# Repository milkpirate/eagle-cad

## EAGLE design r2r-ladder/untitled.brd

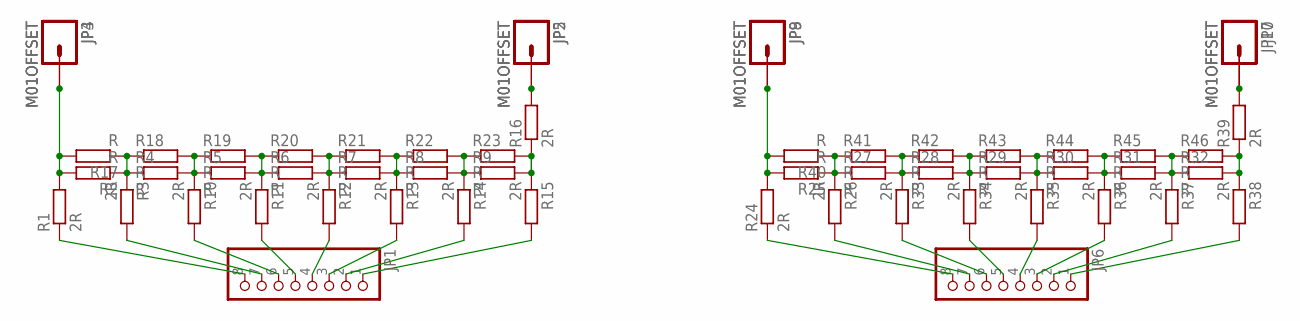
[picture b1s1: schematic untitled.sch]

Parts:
JP1, JP6: PINHD-1X8/90; 1X08/90
JP2, JP3, JP4, JP5, JP7, JP8, JP9, JP10: M01OFFSET; 1X01_OFFSET
R1, R3, R10, R11, R12, R13, R14, R15, R16: 2R; M0805
R2, R4, R5, R6, R7, R8, R9, R17, R18, R19, R20, R21, R22, R23: R; M0805
R24, R26, R33, R34, R35, R36, R37, R38, R39: 2R; 0204V
R25, R27, R28, R29, R30, R31, R32, R40, R41, R42, R43, R44, R45, R46: R; 0204V

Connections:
unnamed: R2.1, R3.1, R4.1
unnamed: R4.2, R5.1, R10.1
unnamed: R5.2, R6.1, R11.1
unnamed: R6.2, R7.1, R12.1
unnamed: R8.2, R9.1, R14.1
unnamed: R7.2, R8.1, R13.1
unnamed: JP3.1, JP4.1, R1.2, R2.2, R17.2
unnamed: JP1.8, R1.1
unnamed: JP1.7, R3.2
unnamed: JP1.6, R10.2
unnamed: JP1.5, R11.2
unnamed: JP1.4, R12.2
unnamed: JP1.3, R13.2
unnamed: JP1.2, R14.2
unnamed: R9.2, R15.1, R16.1
unnamed: JP1.1, R15.2
unnamed: JP2.1, JP5.1, R16.2
unnamed: R25.1, R26.1, R27.1
unnamed: R27.2, R28.1, R33.1
unnamed: R28.2, R29.1, R34.1
unnamed: R29.2, R30.1, R35.1
unnamed: R31.2, R32.1, R37.1
unnamed: R30.2, R31.1, R36.1
unnamed: JP8.1, JP9.1, R24.2, R25.2, R40.2
unnamed: JP6.8, R24.1
unnamed: R17.1, R18.1
unnamed: R18.2, R19.1
unnamed: R19.2, R20.1
unnamed: R20.2, R21.1
unnamed: R22.2, R23.1
unnamed: R21.2, R22.1
unnamed: JP6.7, R26.2
unnamed: JP6.6, R33.2
unnamed: JP6.5, R34.2
unnamed: JP6.4, R35.2
unnamed: JP6.3, R36.2
unnamed: JP6.2, R37.2
unnamed: R32.2, R38.1, R39.1, R46.2
unnamed: JP6.1, R38.2
unnamed: JP7.1, JP10.1, R39.2
unnamed: R40.1, R41.1
unnamed: R41.2, R42.1
unnamed: R42.2, R43.1
unnamed: R43.2, R44.1
unnamed: R45.2, R46.1
unnamed: R44.2, R45.1

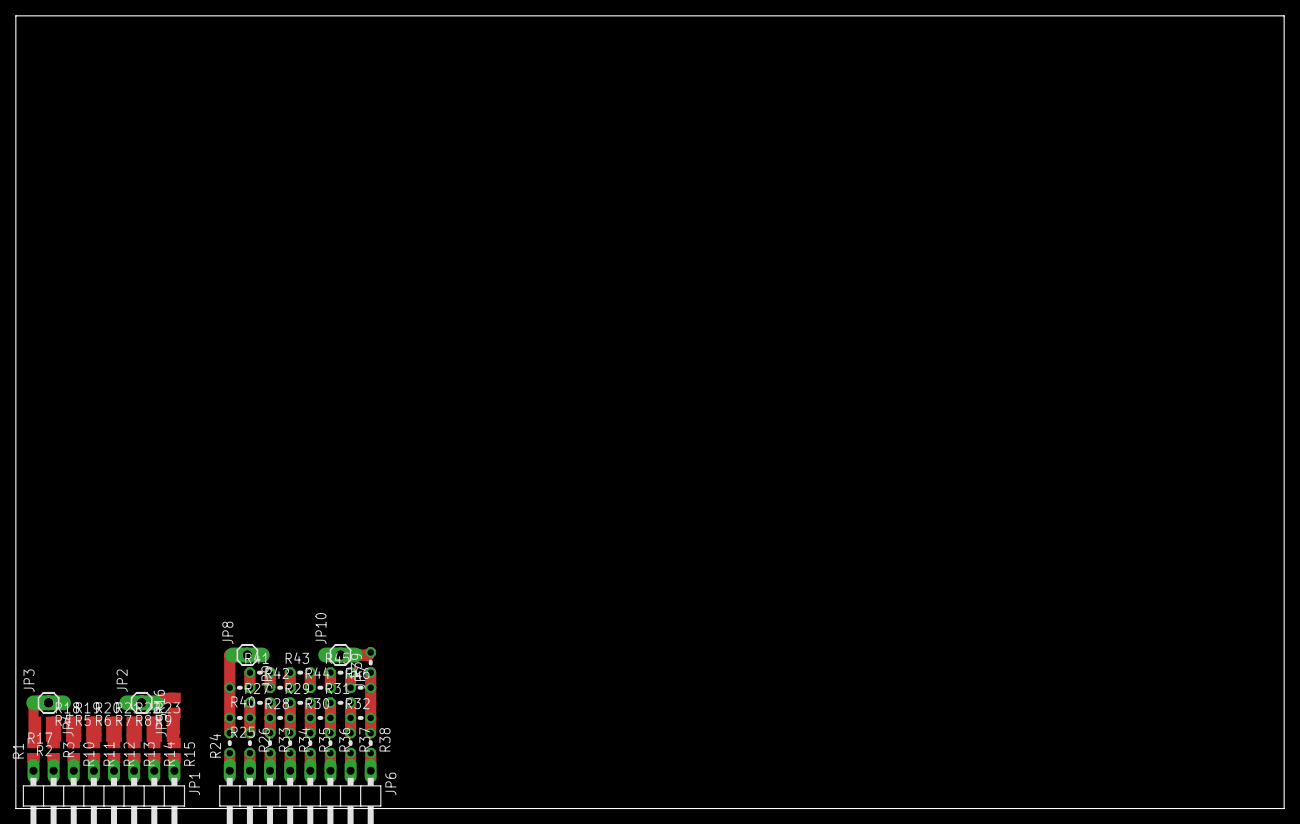
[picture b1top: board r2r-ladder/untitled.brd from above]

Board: 2 copper layers, 160.0 x 100.0 mm, 56 parts (0 on the bottom side), 46 nets.

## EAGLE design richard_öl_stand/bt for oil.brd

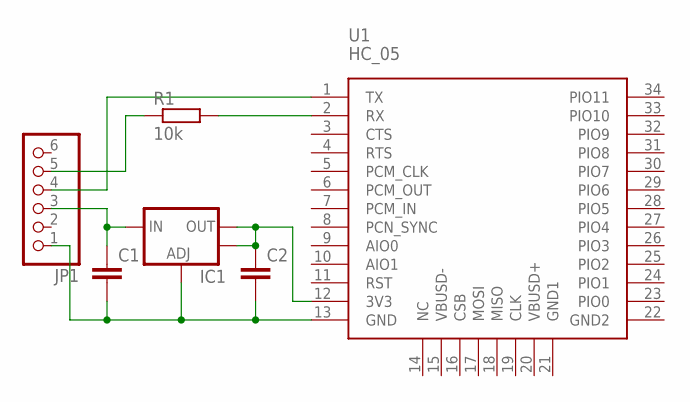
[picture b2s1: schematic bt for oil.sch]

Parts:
C1, C2: C-EUC0805; C0805
IC1: V_REG_LM1117SOT223; SOT223
JP1: PINHD-1X6/90; 1X06/90
R1: 10k; M0805
U1: HC_05; BLUETOOTH_SMD

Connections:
3V3: C2.1, IC1.2 (OUT), IC1.4 (OUT), U1.12 (3V3)
5V: C1.1, IC1.3 (IN), JP1.3
GND: C1.2, C2.2, IC1.1 (ADJ), JP1.1, U1.13 (GND)
unnamed: R1.2, U1.2 (RX)
RX: JP1.5, R1.1
TX: JP1.4, U1.1 (TX)

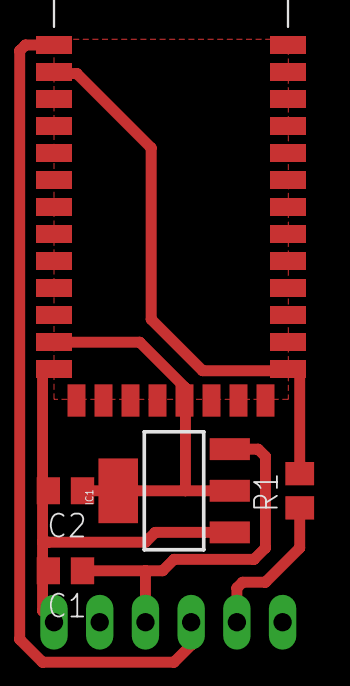
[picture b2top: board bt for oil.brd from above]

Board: 2 copper layers, 6 parts (1 on the bottom side), 6 nets.

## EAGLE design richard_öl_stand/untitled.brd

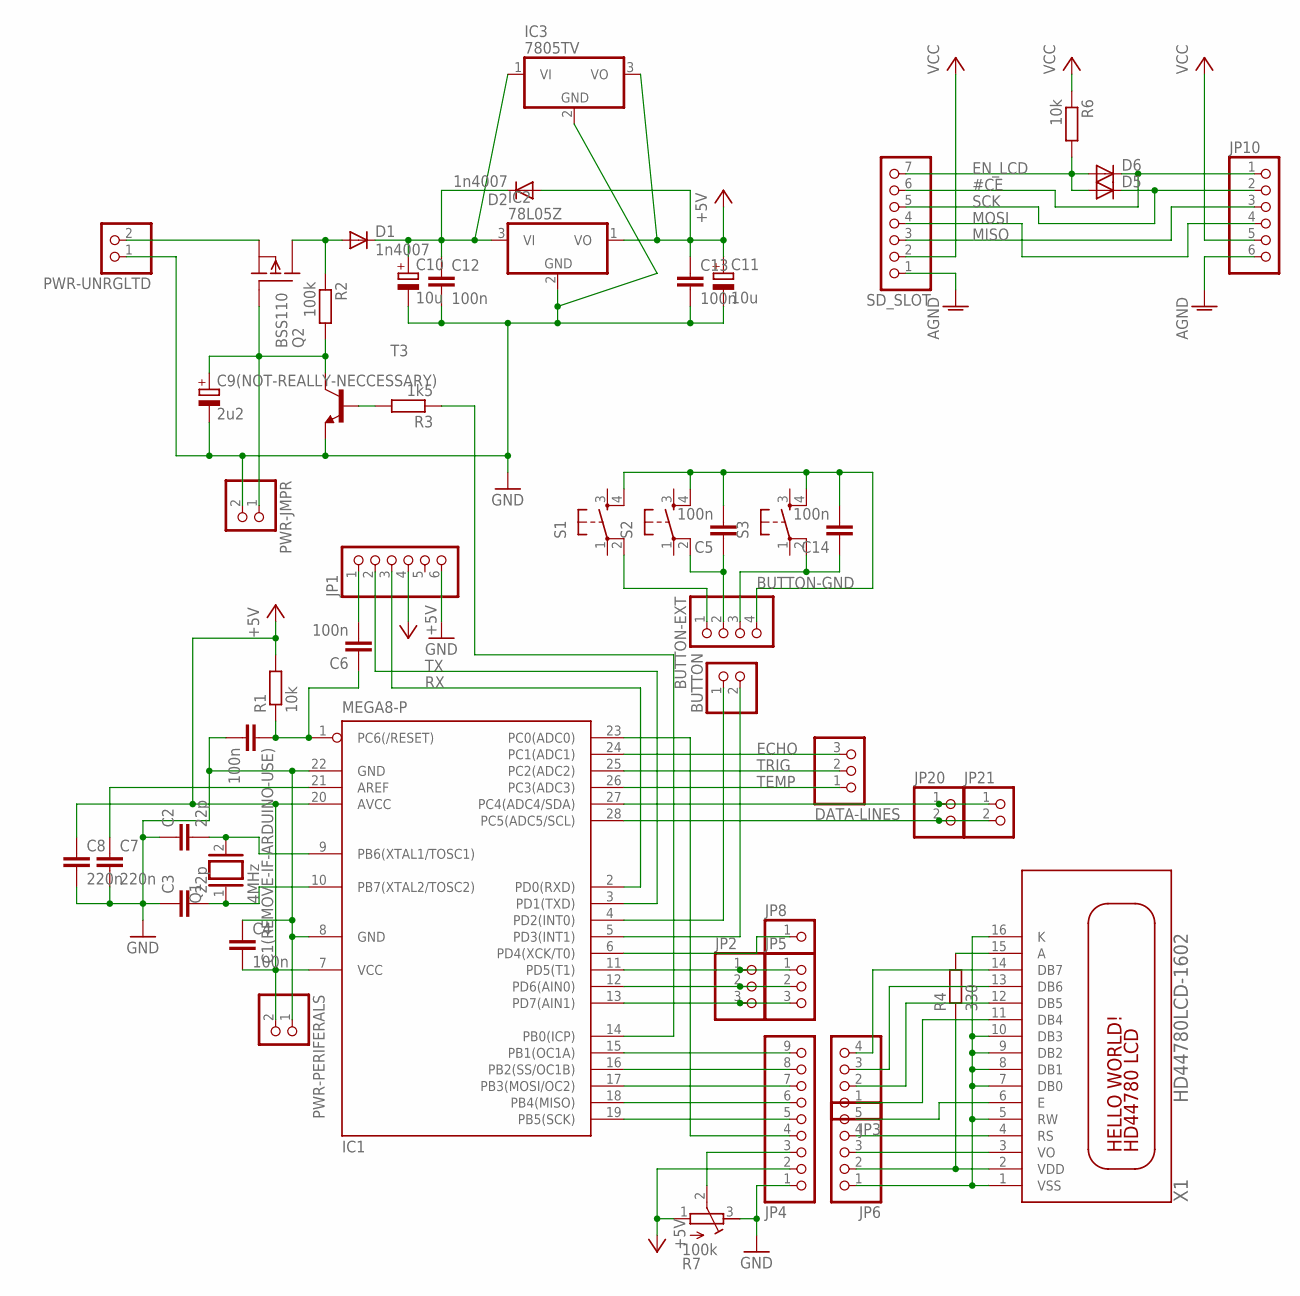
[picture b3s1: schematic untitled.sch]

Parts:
BUTTON: PINHD-1X2; 1X02
BUTTON-EXT: PINHD-1X4; 1X04
C1(REMOVE-IF-ARDUINO-USE), C4, C5, C6, C12, C13, C14: 100n; C025-025X050
C2, C3: 22p; C025-025X050
C7, C8: 220n; C025-025X050
C9(NOT-REALLY-NECCESSARY): 2u2; E2,5-6
C10: 10u; E2,5-6
C11: 10u; E5R
D1, D2: 1n4007; D-2.5
D5: DIODE-D-5; D-5
D6: DIODE-D-2.5; D-2.5
DATA-LINES: PINHD-1X3; 1X03
IC1: MEGA8-P; DIL28-3
IC2: 78L05Z; TO92
IC3: 7805TV; TO220V
JP1, JP10: PINHD-1X6; 1X06
JP2, JP5: PINHD-1X3; 1X03
JP3: PINHD-1X4; 1X04
JP4: PINHD-1X9; 1X09
JP6: PINHD-1X5; 1X05
JP8: PINHD-1X1; 1X01
JP20, JP21: PINHD-1X2; 1X02
PWR-JMPR: PINHD-1X2; 1X02
PWR-PERIFERALS: PINHD-1X2; 1X02
PWR-UNRGLTD: PINHD-1X2; 1X02
Q1: 4MHz; QS
Q2: BSS110; TO92
R1: 10k; 0207/2V
R2: 100k; 0207/2V
R3: 1k5; 0207/2V
R4: 330; 0207/10
R6: 10k; 0207/12
R7: 100k; RTRIM64W
S1, S2, S3: TAC_SWITCHPTH; TACTILE-PTH
SD_SLOT: PINHD-1X7; 1X07
T3: BC167-NPN-TO92-ECB; TO92-ECB
X1: HD44780LCD-1602; LCD1602

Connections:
#CE: D6.C, JP10.1, SD_SLOT.6
+5V: C4.2, C8.1, C11.+, C13.1, D2.A, IC1.7 (VCC), IC1.20 (AVCC), IC2.1 (VO), IC3.3 (VO), JP1.4, JP4.2, PWR-PERIFERALS.2, R1.2, R7.1 (A)
AGND: JP10.6, SD_SLOT.1
BUTTON-GND: BUTTON-EXT.4, C5.2, C14.2, S1.4, S2.4, S3.4
ECHO: DATA-LINES.3, IC1.24 (PC1(ADC1))
EN_LCD: D5.A, D6.A, R6.2, SD_SLOT.7
GND: C1(REMOVE-IF-ARDUINO-USE).2, C2.1, C3.1, C4.1, C7.2, C8.2, C9(NOT-REALLY-NECCESSARY).-, C10.-, C11.-, C12.2, C13.2, IC1.8 (GND), IC1.22 (GND), IC2.2 (GND), IC3.2 (GND), JP1.6, JP4.1, PWR-JMPR.2, PWR-PERIFERALS.1, PWR-UNRGLTD.1, R7.3 (E), T3.E
MISO: JP10.3, SD_SLOT.3
MOSI: JP10.4, SD_SLOT.4
unnamed: C6.2, JP1.1
unnamed: JP4.3, R7.2 (S)
unnamed: R4.2, X1.15 (A)
unnamed: JP3.2, X1.12 (DB5)
unnamed: JP3.3, X1.13 (DB6)
unnamed: JP3.4, X1.14 (DB7)
unnamed: JP3.1, X1.11 (DB4)
unnamed: JP6.5, X1.6 (E)
unnamed: IC1.15 (PB1(OC1A)), JP4.9
unnamed: JP6.4, X1.4 (RS)
unnamed: JP6.3, X1.3 (VO)
unnamed: IC1.16 (PB2(SS/OC1B)), JP4.8
unnamed: IC1.17 (PB3(MOSI/OC2)), JP4.7
unnamed: IC1.18 (PB4(MISO)), JP4.6
unnamed: IC1.19 (PB5(SCK)), JP4.5
unnamed: IC1.23 (PC0(ADC0)), JP4.4
unnamed: C1(REMOVE-IF-ARDUINO-USE).1, C6.1, IC1.1 (PC6(/RESET)), R1.1
unnamed: BUTTON.1, IC1.4 (PD2(INT0))
unnamed: C2.2, IC1.9 (PB6(XTAL1/TOSC1)), Q1.2
unnamed: C3.2, IC1.10 (PB7(XTAL2/TOSC2)), Q1.1
unnamed: IC1.13 (PD7(AIN1)), JP2.3, JP5.3
unnamed: IC1.12 (PD6(AIN0)), JP2.2, JP5.2
unnamed: C7.1, IC1.21 (AREF)
unnamed: IC1.11 (PD5(T1)), JP2.1, JP5.1
unnamed: C9(NOT-REALLY-NECCESSARY).+, PWR-JMPR.1, Q2.2 (G), R2.2, T3.C
unnamed: R3.2, T3.B
unnamed: BUTTON.2, IC1.5 (PD3(INT1))
unnamed: PWR-UNRGLTD.2, Q2.1 (S)
unnamed: D1.A, Q2.3 (D), R2.1
unnamed: BUTTON-EXT.3, C14.1, S3.2
unnamed: IC1.27 (PC4(ADC4/SDA)), JP20.1, JP21.1
unnamed: IC1.28 (PC5(ADC5/SCL)), JP20.2, JP21.2
unnamed: C10.+, C12.1, D1.C, D2.C, IC2.3 (VI), IC3.1 (VI)
unnamed: IC1.6 (PD4(XCK/T0)), JP8.1
unnamed: BUTTON-EXT.2, C5.1, S2.2
unnamed: IC1.14 (PB0(ICP)), R3.1
unnamed: BUTTON-EXT.1, S1.2
RX: IC1.2 (PD0(RXD)), JP1.3
SCK: D5.C, JP10.2, SD_SLOT.5
TEMP: DATA-LINES.1, IC1.26 (PC3(ADC3))
TRIG: DATA-LINES.2, IC1.25 (PC2(ADC2))
TX: IC1.3 (PD1(TXD)), JP1.2
VCC: JP10.5, R6.1, SD_SLOT.2
VDD: JP6.2, R4.1, X1.2 (VDD)
VSS: JP6.1, X1.1 (VSS), X1.5 (RW), X1.7 (DB0), X1.8 (DB1), X1.9 (DB2), X1.10 (DB3), X1.16 (K)

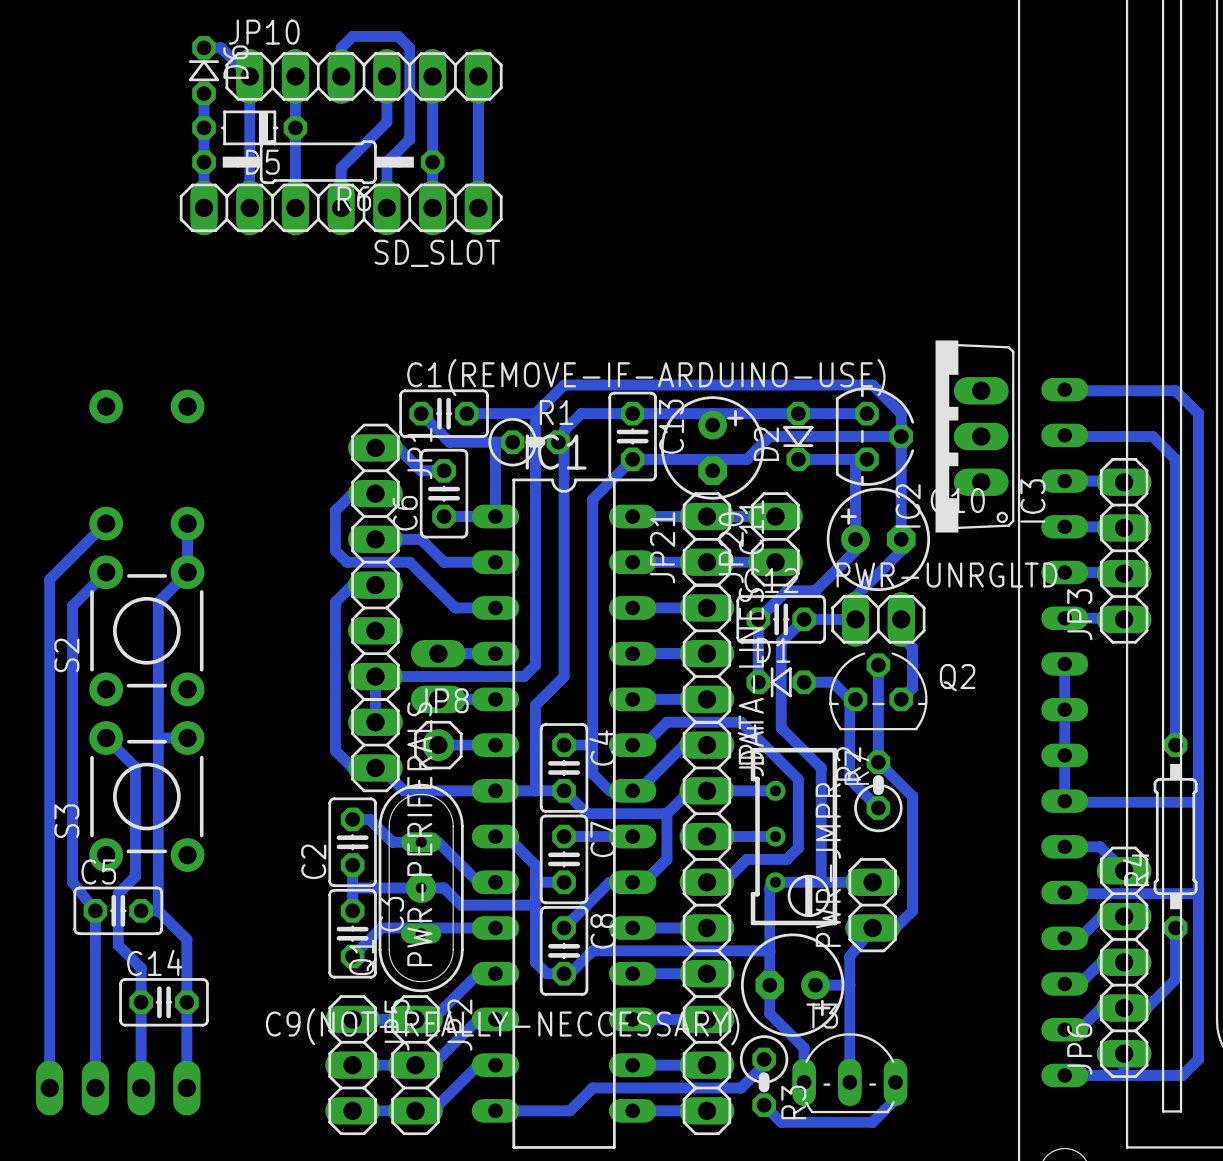
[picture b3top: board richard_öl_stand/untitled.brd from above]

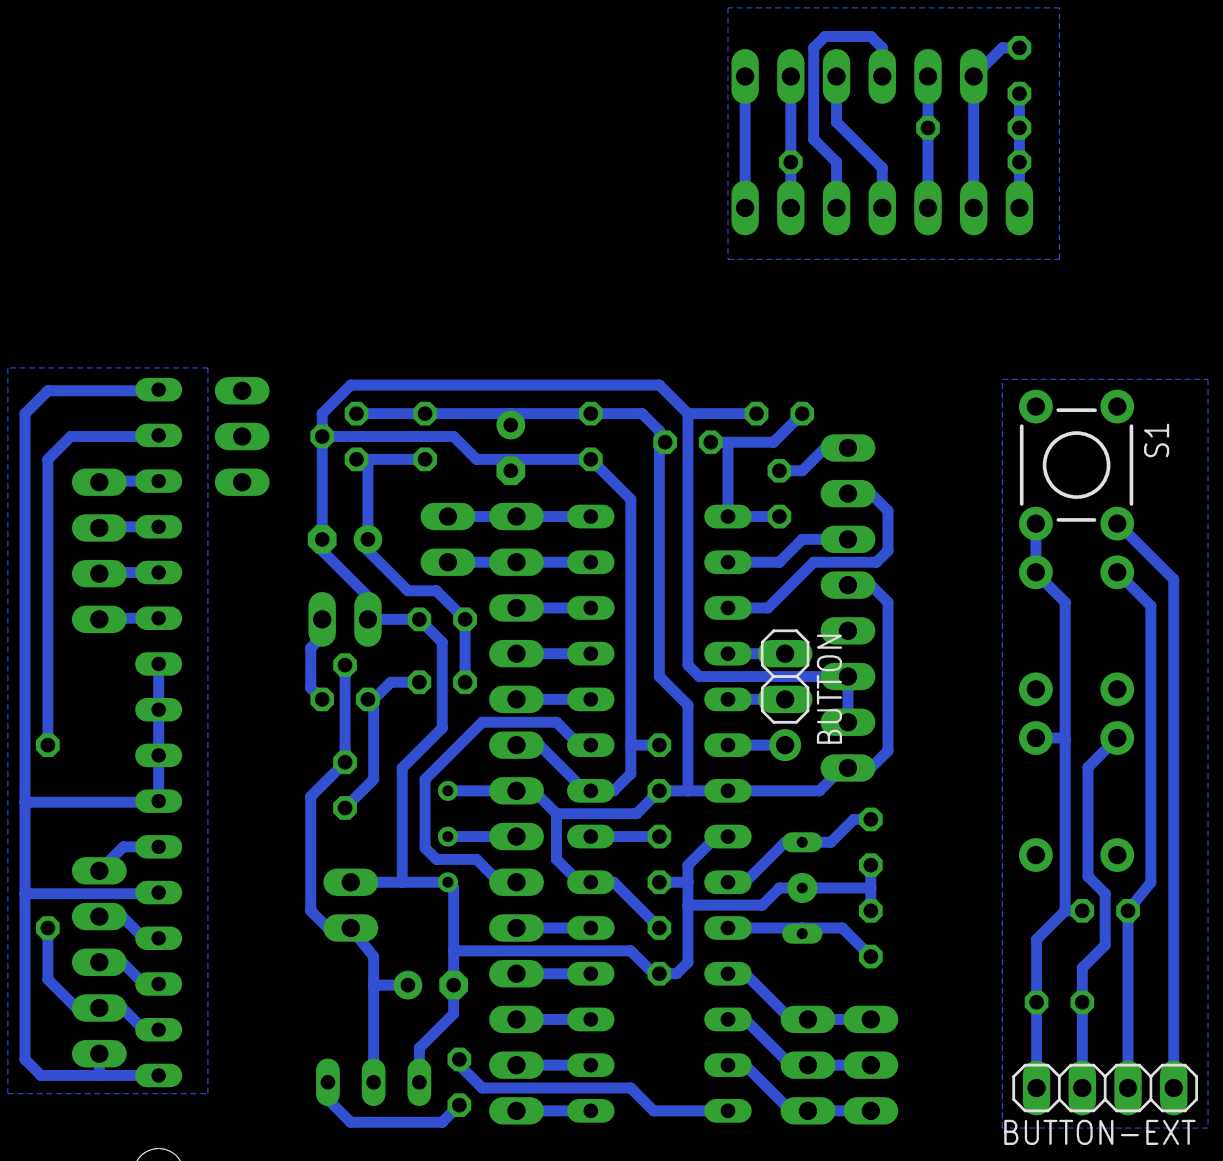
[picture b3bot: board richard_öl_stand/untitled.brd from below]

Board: 2 copper layers, 51 parts (3 on the bottom side), 54 nets.

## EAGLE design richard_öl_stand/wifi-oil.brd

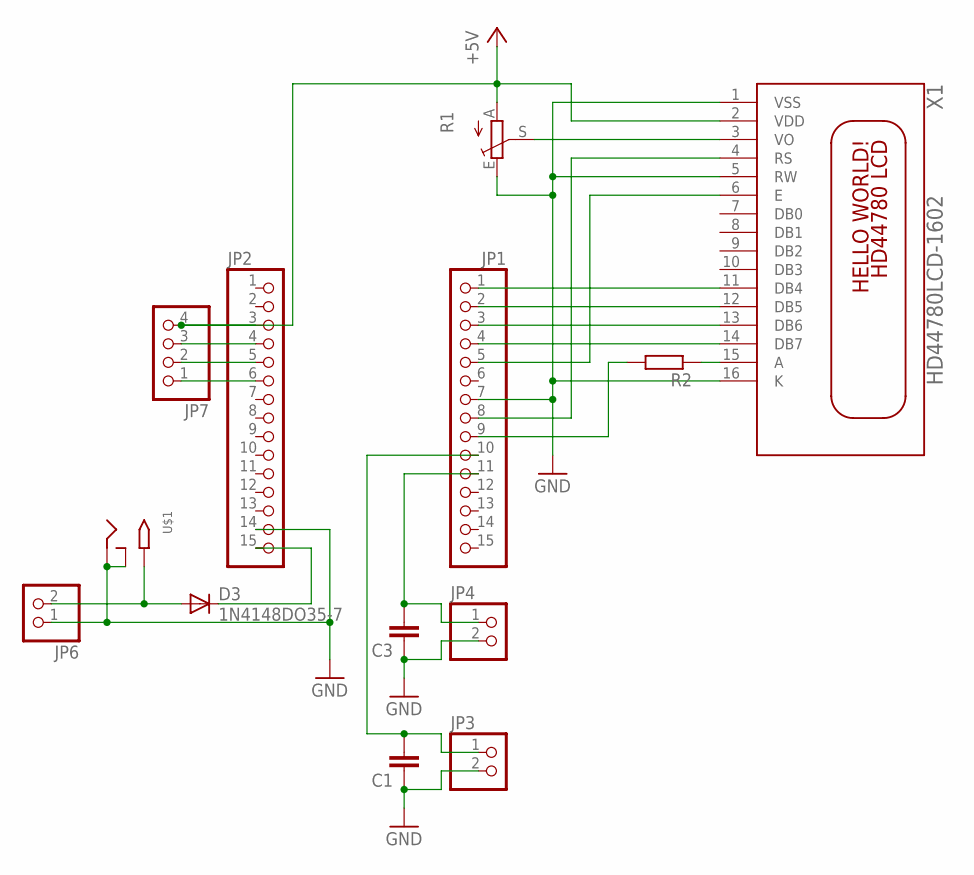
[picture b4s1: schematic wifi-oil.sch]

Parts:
C1, C3: C-EU025-025X050; C025-025X050
D3: 1N4148DO35-7; DO35-7
JP1, JP2: PINHD-1X15; 1X15
JP3, JP4, JP6: PINHD-1X2; 1X02
JP7: PINHD-1X4; 1X04
R1: TRIM_EU-RS3; RS3
R2: R-EU_0204/7; 0204/7
U$1: 2.1MMJACKTHM; PJ-102A
X1: HD44780LCD-1602; LCD1602

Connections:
GND: C1.1, C3.1, JP1.7, JP2.14, JP3.2, JP4.2, JP6.1, R1.E, U$1.RING, U$1.RING_SW, X1.1 (VSS), X1.5 (RW), X1.16 (K)
unnamed: JP1.4, X1.14 (DB7)
unnamed: JP1.3, X1.13 (DB6)
unnamed: JP1.2, X1.12 (DB5)
unnamed: JP1.1, X1.11 (DB4)
unnamed: JP1.9, R2.2
unnamed: R1.S, X1.3 (VO)
unnamed: C1.2, JP1.10, JP3.1
unnamed: JP2.6, JP7.1
unnamed: JP1.8, X1.4 (RS)
unnamed: JP1.5, X1.6 (E)
unnamed: JP2.5, JP7.2
unnamed: R2.1, X1.15 (A)
unnamed: JP2.4, JP7.3
unnamed: D3.A, JP6.2, U$1.TIP
unnamed: C3.2, JP1.11, JP4.1
unnamed: D3.C, JP2.15
VDD: JP2.3, JP7.4, R1.A, X1.2 (VDD)

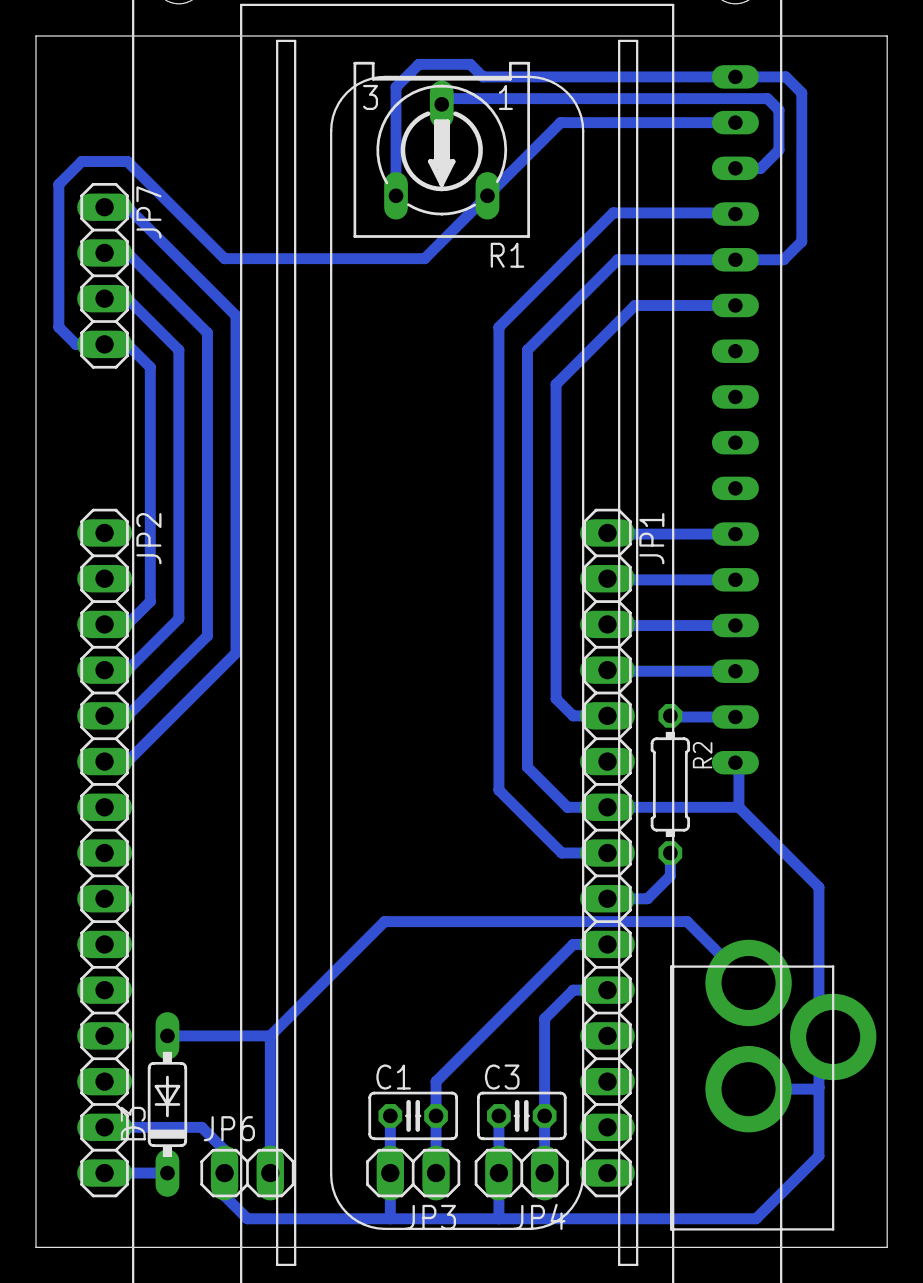
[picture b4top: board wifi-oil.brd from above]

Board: 2 copper layers, 47.3 x 67.3 mm, 13 parts (0 on the bottom side), 18 nets.

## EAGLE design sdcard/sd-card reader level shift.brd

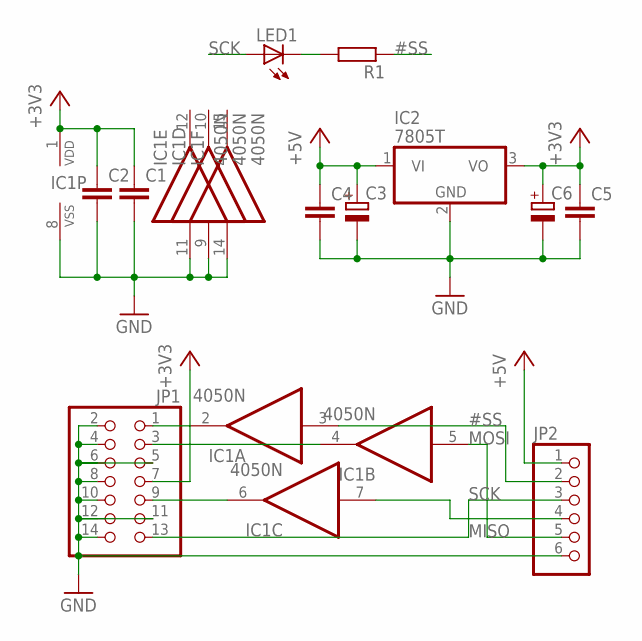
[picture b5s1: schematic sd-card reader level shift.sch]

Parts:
C1, C2, C4, C5: C-EU025-025X050; C025-025X050
C3, C6: CPOL-EUE2.5-5; E2,5-5
IC1: 4050N; DIL16
IC2: 7805T; TO220H
JP1: PINHD-2X7/90; 2X07/90
JP2: PINHD-1X6; 1X06
LED1: LED3MM
R1: R-EU_0204/7; 0204/7

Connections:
#SS: IC1.3 (I), JP2.2, R1.1
+3V3: C1.1, C2.1, C5.1, C6.+, IC1.1 (VDD), IC2.3 (VO), JP1.7
+5V: C3.+, C4.1, IC2.1 (VI), JP2.1
GND: C1.2, C2.2, C3.-, C4.2, C5.2, C6.-, IC1.8 (VSS), IC1.9 (I), IC1.11 (I), IC1.14 (I), IC2.2 (GND), JP1.2, JP1.4, JP1.5, JP1.6, JP1.8, JP1.10, JP1.11, JP1.12, JP1.14, JP2.6
MISO: JP1.13, JP2.3
MOSI: IC1.5 (I), JP2.5
unnamed: IC1.2 (O), JP1.1
unnamed: IC1.4 (O), JP1.3
unnamed: IC1.6 (O), JP1.9
unnamed: LED1.K (C), R1.2
SCK: IC1.7 (I), JP2.4, LED1.A

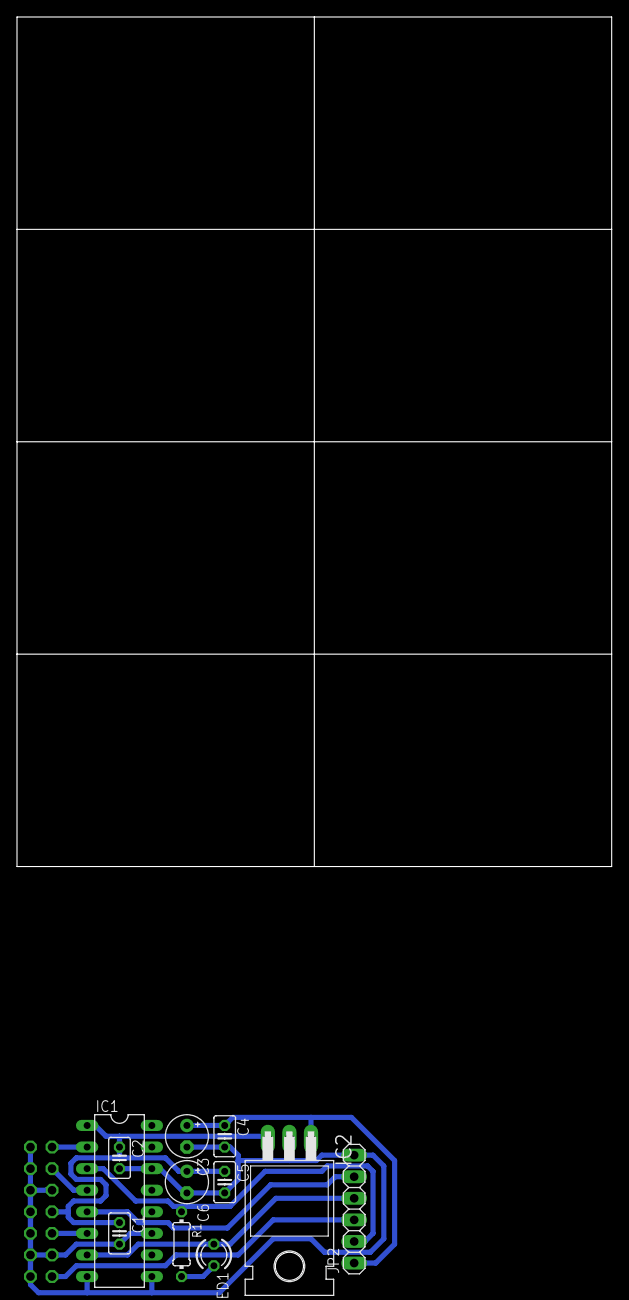
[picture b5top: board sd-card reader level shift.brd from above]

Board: 2 copper layers, 70.0 x 100.0 mm, 12 parts (1 on the bottom side), 11 nets.

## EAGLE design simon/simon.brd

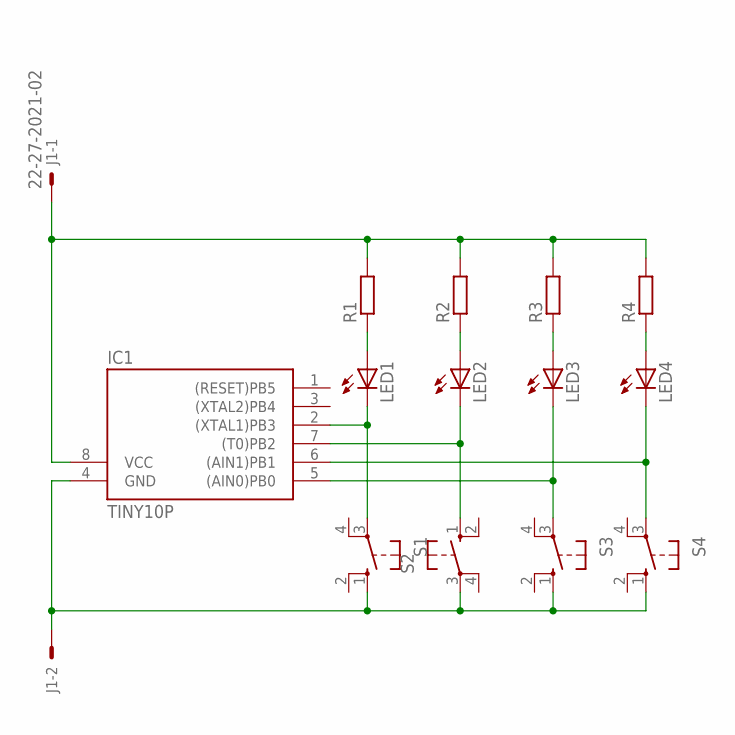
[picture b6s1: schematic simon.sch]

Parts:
IC1: TINY10P; DIL08
J1: 22-27-2021-02; 6410-02
LED1, LED2, LED3, LED4: LED3MM
R1, R2, R3, R4: R-EU_0204/2V; 0204V
S1, S2, S3, S4: 10-XX; B3F-10XX

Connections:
GND: IC1.4 (GND), J1.2, S1.1 (S), S2.3, S3.1 (S), S4.1 (S)
unnamed: IC1.8 (VCC), J1.1, R1.2, R2.2, R3.2, R4.2
unnamed: LED4.A, R4.1
unnamed: LED3.A, R3.1
unnamed: LED2.A, R2.1
unnamed: LED1.A, R1.1
unnamed: IC1.2 ((XTAL1)PB3), LED1.K (C), S1.3
unnamed: IC1.7 ((T0)PB2), LED2.K (C), S2.1 (S)
unnamed: IC1.5 ((AIN0)PB0), LED3.K (C), S3.3
unnamed: IC1.6 ((AIN1)PB1), LED4.K (C), S4.3

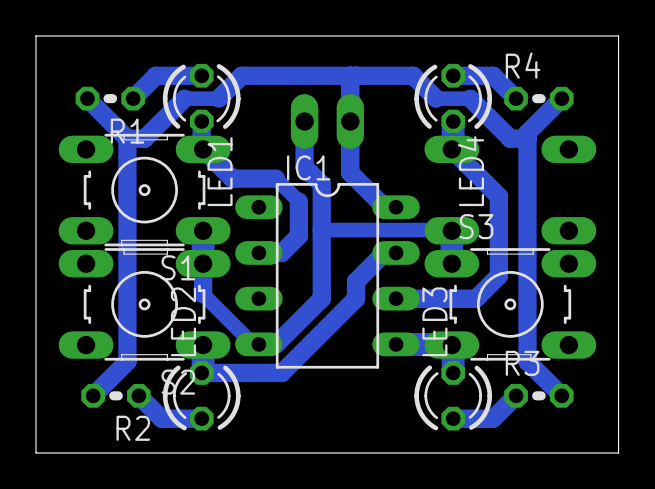
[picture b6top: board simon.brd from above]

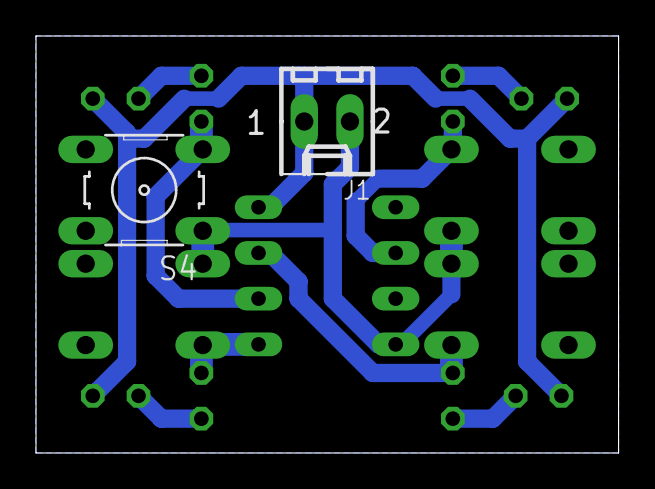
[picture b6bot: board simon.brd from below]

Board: 2 copper layers, 32.4 x 23.2 mm, 14 parts (2 on the bottom side), 10 nets.

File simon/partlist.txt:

Partlist

Exported from simon_SMD.sch at 21.05.2013 23:48:45

EAGLE Version 6.1.0 Copyright (c) 1988-2012 CadSoft

Assembly variant: 

Part     Value          Device          Package      Library      Sheet

BAT1                    SN2032          SN2032       sn2032       1
LED1                    LEDCHIP-LED0805 CHIP-LED0805 led          1
LED2                    LEDCHIP-LED0805 CHIP-LED0805 led          1
LED3                    LEDCHIP-LED0805 CHIP-LED0805 led          1
LED4                    LEDCHIP-LED0805 CHIP-LED0805 led          1
R1                      R-EU_M0805      M0805        rcl          1
R2                      R-EU_M0805      M0805        rcl          1
R3                      R-EU_M0805      M0805        rcl          1
R4                      R-EU_M0805      M0805        rcl          1
T1       EVQQ2          EVQQ2           EVQ-Q2       adafruit_t10 1
T2       EVQQ2          EVQQ2           EVQ-Q2       adafruit_t10 1
T3       EVQQ2          EVQQ2           EVQ-Q2       adafruit_t10 1
T4       EVQQ2          EVQQ2           EVQ-Q2       adafruit_t10 1
U$1      ATTINY10       ATTINY10        SOT23-6      adafruit_t10 1

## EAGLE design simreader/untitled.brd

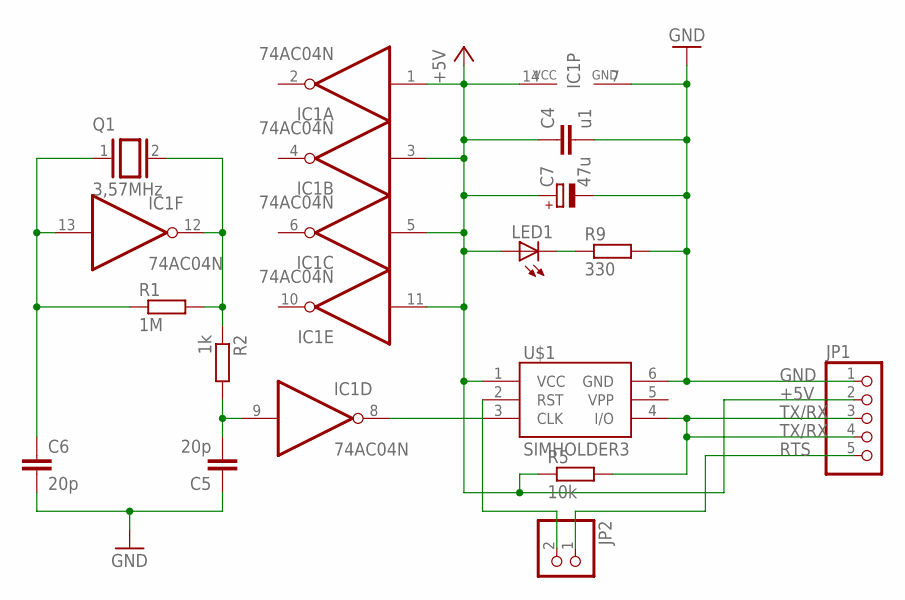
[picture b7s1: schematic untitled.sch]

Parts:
C4: u1; C025-025X050
C5, C6: 20p; C025-025X050
C7: 47u; E2,5-6E
IC1: 74AC04N; DIL14
JP1: PINHD-1X5/90; 1X05/90
JP2: PINHD-1X2; 1X02
LED1: LED3MM
Q1: 3,57MHz; QS
R1: 1M; 0207/2V
R2: 1k; 0207/2V
R5: 10k; 0207/2V
R9: 330; 0207/2V
U$1: SIMHOLDER3

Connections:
+5V: C4.1, C7.+, IC1.1 (I), IC1.3 (I), IC1.5 (I), IC1.11 (I), IC1.14 (VCC), JP1.2, LED1.A, R5.1, U$1.1 (VCC)
GND: C4.2, C5.1, C6.2, C7.-, IC1.7 (GND), JP1.1, R9.2, U$1.6 (GND)
unnamed: C5.2, IC1.9 (I), R2.2
unnamed: C6.1, IC1.13 (I), Q1.1, R1.1
unnamed: LED1.K (C), R9.1
unnamed: IC1.8 (O), U$1.3 (CLK)
unnamed: IC1.12 (O), Q1.2, R1.2, R2.1
unnamed: JP2.2, U$1.2 (RST)
RTS: JP1.5, JP2.1
TX/RX: JP1.3, JP1.4, R5.2, U$1.4 (I/O)

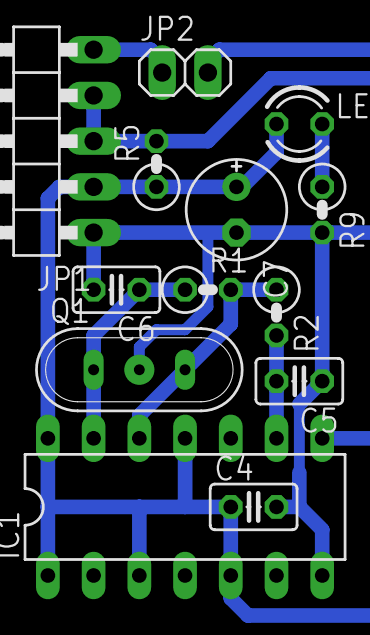
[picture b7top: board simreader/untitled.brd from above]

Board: 2 copper layers, 14 parts (1 on the bottom side), 10 nets.

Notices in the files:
parts and their libraries:
SparkFun-Connectors: Licensing: CC v3.0 Share-Alike You are welcome to use this library for commercial purposes.
